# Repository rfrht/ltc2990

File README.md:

# LTC2990

**I2C comms with Linear LTC 2990 Quad I2C Voltage, Current and Temperature Monitor**

This project describes how to access and obtain register data from a LTC2990 IC.
It is preconfigured to run on mode `0b1011111`, it means: V1, V2, V3, V4; All Measurements per Mode, Single Acquisition and Temperature reported in Celsius.

Don't forget to read the [datasheet](http://www.linear.com/product/LTC2990)!

Sample output:

~~~
root@raspberrypi:~# python i2c-ltc2990.py
Int. Temp. : 30 C
Voltage V1 : 3.29624918 V
Voltage V2 : 3.29624918 V
Voltage V3 : 3.29624918 V
Voltage V4 : 3.29624918 V
Vin        : 3.2949939 V
~~~

*[RepRap Ltd](https://github.com/RepRapLtd/Walking-robots/tree/main/Petoi) created a [forked version](https://github.com/RepRapLtd/Walking-robots/blob/main/Petoi/Software/Pi/rrlpetoi.py) that provides continous readings*

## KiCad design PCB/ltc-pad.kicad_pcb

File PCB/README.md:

# LTC2990 sample PCB

**A simple board for tests**

This board was designed in [KiCad EDA](http://www.kicad-pcb.org/). Requires [MSOP-10](https://github.com/mcous/kicad-lib/blob/master/footprints/sop.pretty/MSOP10.kicad_mod) footprints.

Please refer to the PNG image for the sample output.

If you live in Brazil, you can order this board from [Curta Circuitos](http://curtacircuitos.com.br/rfreire/ltc2990).

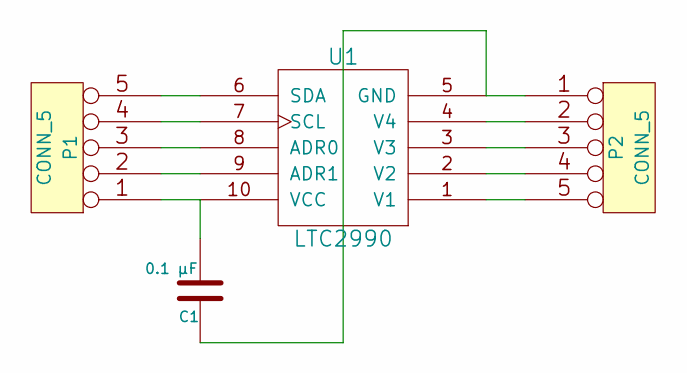
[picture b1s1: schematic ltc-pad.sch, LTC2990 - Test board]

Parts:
C1: 0.1 µF
P1, P2: CONN_5
U1: LTC2990

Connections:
unnamed: P2.5, U1.1 (V1)
unnamed: C1.1, P2.1, U1.5 (GND)
unnamed: C1.2, P1.1, U1.10 (VCC)
unnamed: P1.2, U1.9 (ADR1)
unnamed: P1.3, U1.8 (ADR0)
unnamed: P1.4, U1.7 (SCL)
unnamed: P1.5, U1.6 (SDA)
unnamed: P2.4, U1.2 (V2)
unnamed: P2.3, U1.3 (V3)
unnamed: P2.2, U1.4 (V4)

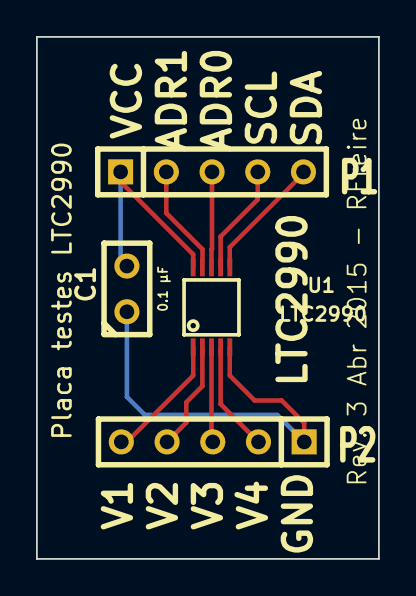
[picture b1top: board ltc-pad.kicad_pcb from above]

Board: 2 copper layers, 19.0 x 29.0 mm, 4 parts (0 on the bottom side), 10 nets.

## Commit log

2015-04-13 Initial release
2015-04-13 Added sample output
2015-04-26 Added licensing info, added sample usage for TR modes
2015-04-26 Updated command output to reflect code change in internal temperature
2015-04-26 Initial commit: sample test board
2015-04-26 Added ADR0 and ADR1 pro-tip
2015-04-26 Added a link to Curta Circuitos
2015-04-30 Added treatment for startup; 1st collect returned 0
2022-11-08 Added forked driver from RepRap
